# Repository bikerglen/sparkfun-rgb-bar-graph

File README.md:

Some notes:

Altera and Xilinx versions are the same except for the interface used to interface to the CPU. For Xilinx, it's an AXI4-Lite bus. For Intel/Altera it's an Avalon bus.

Minimum value of BASE_DELAY in both versions of code is 22 + (2 * (number of columns)). For the SparkFun RGB bar graph this is 22 + 2 * 16 =  22 + 32 = 54.

Refresh rate is calculated as

	(input clock frequency) / ((number of rows) * (BASE_DELAY) * (2^(bit depth) - 1)

For the SparkFun RGB LED bar graph this works out to

	(50e6) / (16 * 54 * (2^8 - 1)) = 227 Hz

For the DF Robot / Adafruit 64x64 RGB LED panels this works out to

	(50e6) / (32 * (22+2*64) * (2^6 - 1)) = 165 Hz

For my 96 x 64 video "wall" this works out to 

	(50e6) / (16 * 960 * (2^4 - 1)) = 217 Hz

In theory the base delay of 960 for these panels could be lowered to 22 + 2 * 192 = 406.

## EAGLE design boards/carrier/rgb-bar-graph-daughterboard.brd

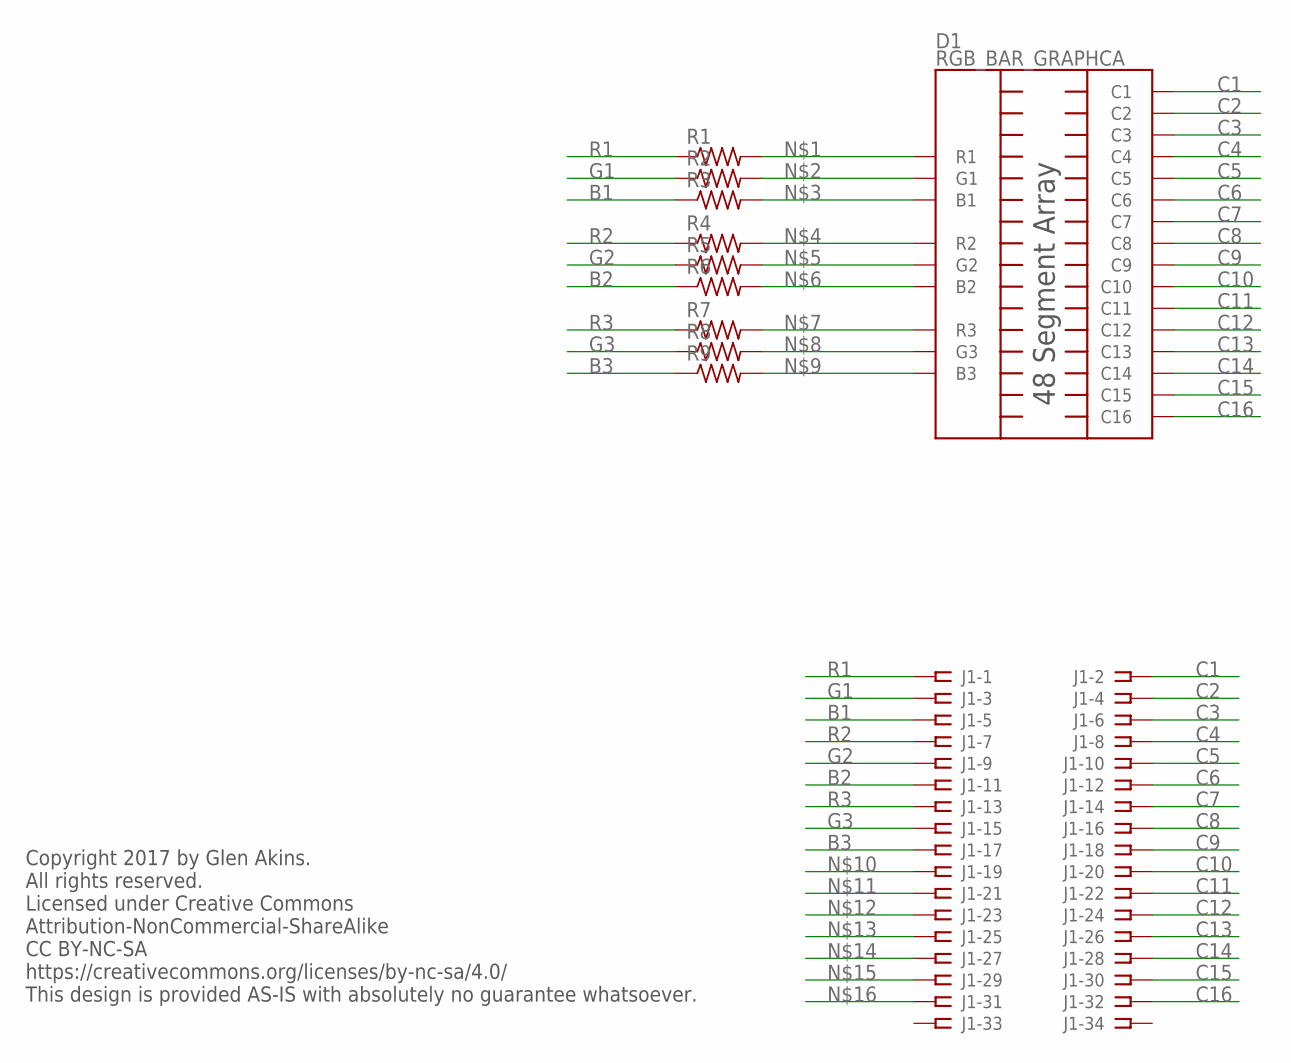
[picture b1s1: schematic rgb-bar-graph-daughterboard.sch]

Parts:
D1: RGB_BAR_GRAPHCA; RGB_BAR_GRAPH
J1: RGB-BAR-GRAPH-2X17-MOD-PADS; RGB-BAR-GRAPH-SMD-34-PIN
R1, R2, R3, R4, R5, R6, R7, R8, R9: R-US_R1206; R1206

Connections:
B1: J1.5, R3.1
B2: J1.11, R6.1
B3: J1.17, R9.1
C1: D1.1 (C1), J1.2
C2: D1.25 (C2), J1.4
C3: D1.3 (C3), J1.6
C4: D1.4 (C4), J1.8
C5: D1.23 (C5), J1.10
C6: D1.5 (C6), J1.12
C7: D1.22 (C7), J1.14
C8: D1.21 (C8), J1.16
C9: D1.20 (C9), J1.18
C10: D1.8 (C10), J1.20
C11: D1.19 (C11), J1.22
C12: D1.18 (C12), J1.24
C13: D1.10 (C13), J1.26
C14: D1.11 (C14), J1.28
C15: D1.15 (C15), J1.30
C16: D1.12 (C16), J1.32
G1: J1.3, R2.1
G2: J1.9, R5.1
G3: J1.15, R8.1
unnamed: D1.9 (R1), R1.2
unnamed: D1.7 (G1), R2.2
unnamed: D1.24 (B1), R3.2
unnamed: D1.17 (R2), R4.2
unnamed: D1.16 (G2), R5.2
unnamed: D1.6 (B2), R6.2
unnamed: D1.13 (R3), R7.2
unnamed: D1.2 (G3), R8.2
unnamed: D1.14 (B3), R9.2
R1: J1.1, R1.1
R2: J1.7, R4.1
R3: J1.13, R7.1

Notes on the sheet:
Copyright 2017 by Glen Akins. All rights reserved. Licensed under Creative Commons Attribution-NonCommercial-ShareAlike CC BY-NC-SA https://creativecommons.org/licenses/by-nc-sa/4.0/ This design is provided AS-IS with absolutely no guarantee whatsoever.

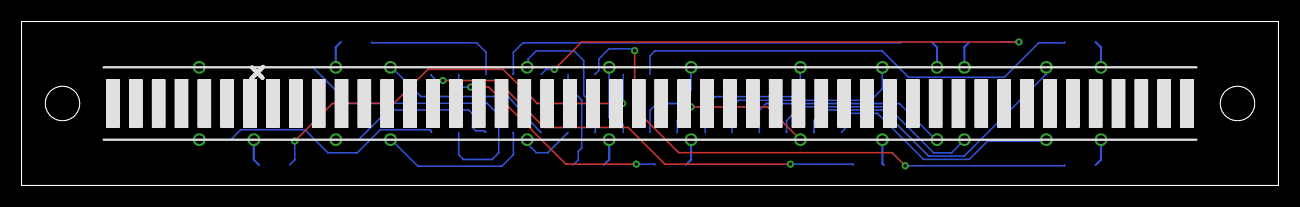
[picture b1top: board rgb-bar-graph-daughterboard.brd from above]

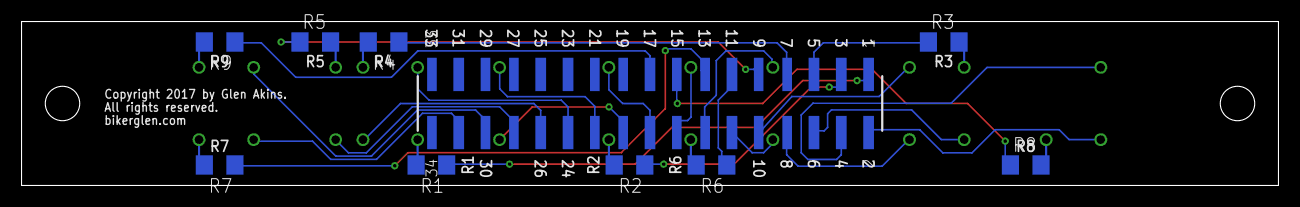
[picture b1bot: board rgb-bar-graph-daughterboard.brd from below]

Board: 2 copper layers, 116.8 x 15.2 mm, 11 parts (10 on the bottom side), 34 nets.

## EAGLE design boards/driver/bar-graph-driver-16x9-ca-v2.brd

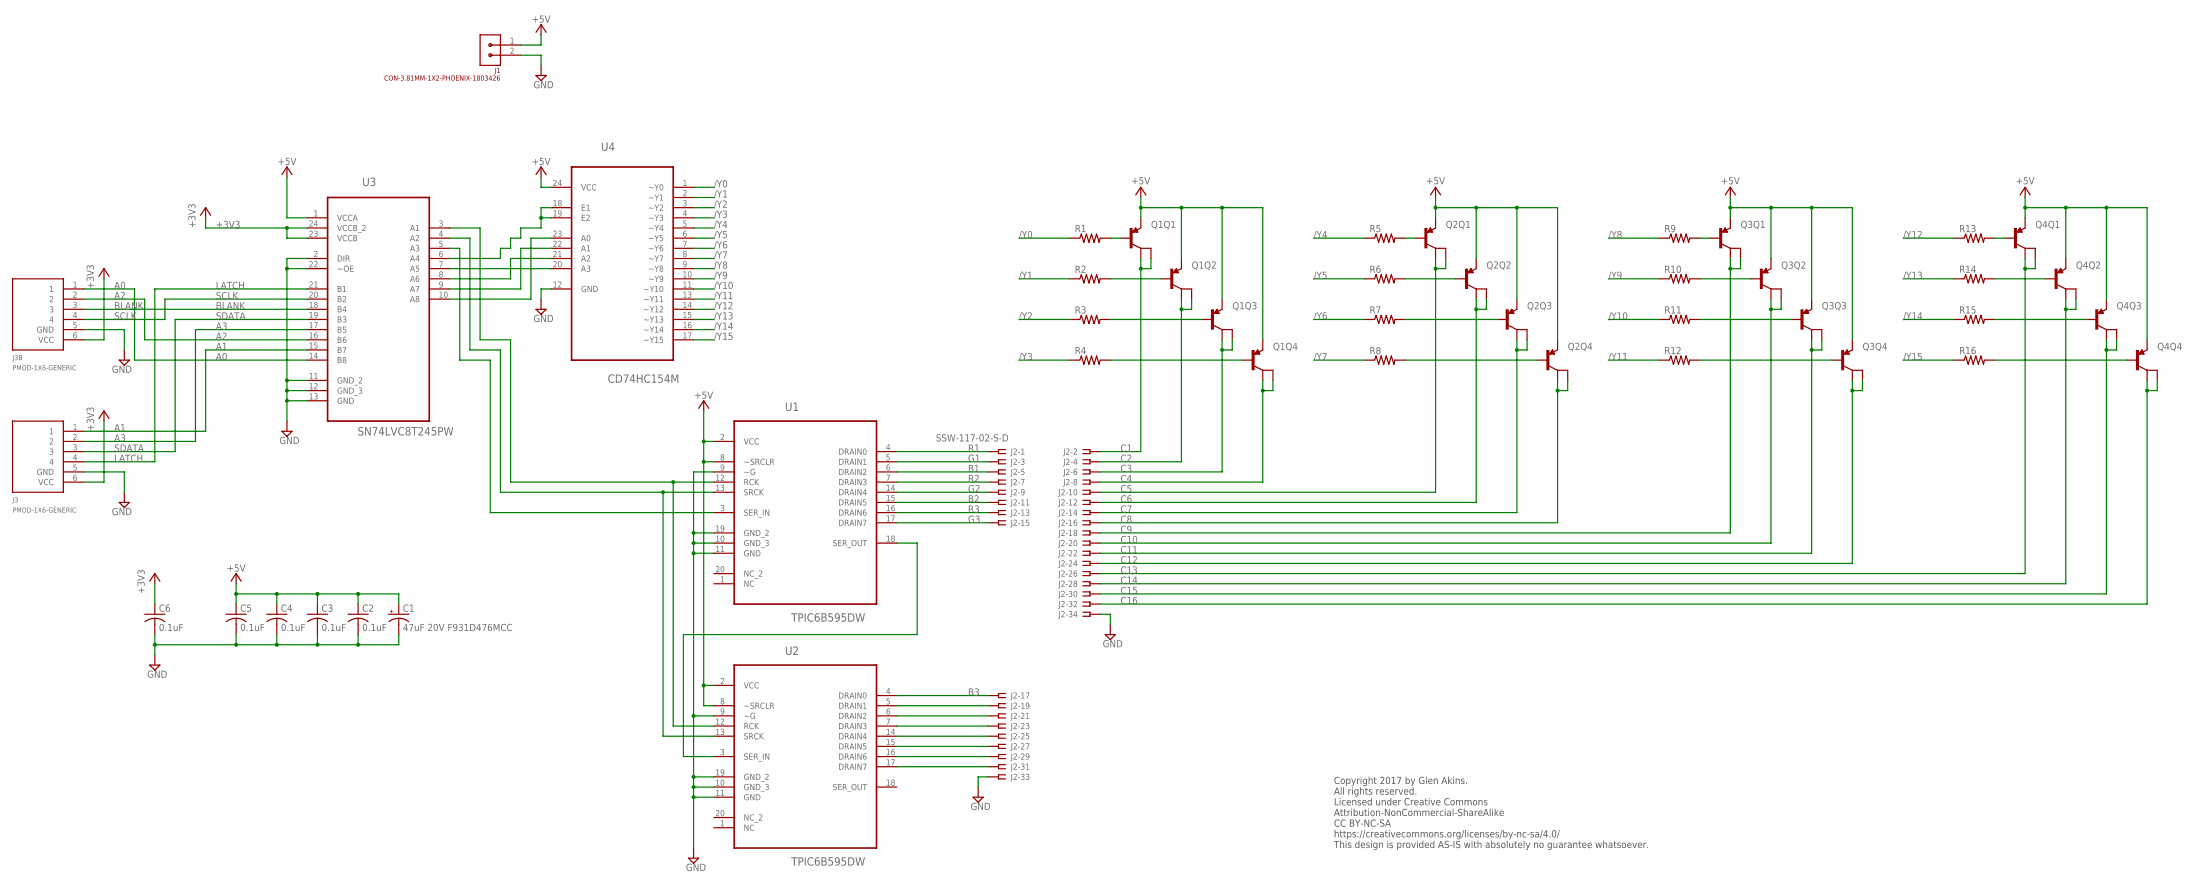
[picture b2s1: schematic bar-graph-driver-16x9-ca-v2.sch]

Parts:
C1: 47uF 20V F931D476MCC; C/6032-28R
C2, C3, C4, C5, C6: 0.1uF; C1206
J1: CON-3.81MM-1X2-PHOENIX-1803426; CON-PHOENIX-1803426-3.81-1X2
J2: SSW-117-02-S-D
J3, J3B: PMOD-1X6-GENERIC; CON-PMOD-1X6
Q1, Q2, Q3, Q4: MMPQ2907A; SO16
R1, R2, R3, R4, R5, R6, R7, R8, R9, R10, R11, R12, R13, R14, R15, R16: R-US_R1206; R1206
U1, U2: TPIC6B595DW; SOIC127P1030X265-20N
U3: SN74LVC8T245PW; SOP65P640X120-24N
U4: CD74HC154M; SOIC127P1030X265-24N

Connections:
+3V3: C6.1, J3.6 (VCC), J3B.6 (VCC), U3.23 (VCCB), U3.24 (VCCB_2)
+5V: C1.+, C2.1, C3.1, C4.1, C5.1, J1.1, Q1.10 (E), Q1.12 (E), Q1.14 (E), Q1.16 (E), Q2.10 (E), Q2.12 (E), Q2.14 (E), Q2.16 (E), Q3.10 (E), Q3.12 (E), Q3.14 (E), Q3.16 (E), Q4.10 (E), Q4.12 (E), Q4.14 (E), Q4.16 (E), U1.2 (VCC), U1.8 (~SRCLR), U2.2 (VCC), U2.8 (~SRCLR), U3.1 (VCCA), U4.24 (VCC)
/Y0: R1.1, U4.1 (~Y0)
/Y1: R2.1, U4.2 (~Y1)
/Y2: R3.1, U4.3 (~Y2)
/Y3: R4.1, U4.4 (~Y3)
/Y4: R5.1, U4.5 (~Y4)
/Y5: R6.1, U4.6 (~Y5)
/Y6: R7.1, U4.7 (~Y6)
/Y7: R8.1, U4.8 (~Y7)
/Y8: R9.1, U4.9 (~Y8)
/Y9: R10.1, U4.10 (~Y9)
/Y10: R11.1, U4.11 (~Y10)
/Y11: R12.1, U4.13 (~Y11)
/Y12: R13.1, U4.14 (~Y12)
/Y13: R14.1, U4.15 (~Y13)
/Y14: R15.1, U4.16 (~Y14)
/Y15: R16.1, U4.17 (~Y15)
A0: J3B.1, U3.14 (B8)
A0_5: U3.10 (A8), U4.23 (A0)
A1: J3.1, U3.15 (B7)
A1_5: U3.9 (A7), U4.22 (A1)
A2: J3B.2, U3.16 (B6)
A2_5: U3.8 (A6), U4.21 (A2)
A3: J3.2, U3.17 (B5)
A3_5: U3.7 (A5), U4.20 (A3)
B1: J2.5, U1.6 (DRAIN2)
B2: J2.11, U1.15 (DRAIN5)
B3: J2.17, U2.4 (DRAIN0)
BLANK: J3B.3, U3.18 (B4)
BLANK_5: U3.6 (A4), U4.18 (E1), U4.19 (E2)
C1: J2.2, Q1.1 (C), Q1.2 (C)
C2: J2.4, Q1.3 (C), Q1.4 (C)
C3: J2.6, Q1.5 (C), Q1.6 (C)
C4: J2.8, Q1.7 (C), Q1.8 (C)
C5: J2.10, Q2.1 (C), Q2.2 (C)
C6: J2.12, Q2.3 (C), Q2.4 (C)
C7: J2.14, Q2.5 (C), Q2.6 (C)
C8: J2.16, Q2.7 (C), Q2.8 (C)
C9: J2.18, Q3.1 (C), Q3.2 (C)
C10: J2.20, Q3.3 (C), Q3.4 (C)
C11: J2.22, Q3.5 (C), Q3.6 (C)
C12: J2.24, Q3.7 (C), Q3.8 (C)
C13: J2.26, Q4.1 (C), Q4.2 (C)
C14: J2.28, Q4.3 (C), Q4.4 (C)
C15: J2.30, Q4.5 (C), Q4.6 (C)
C16: J2.32, Q4.7 (C), Q4.8 (C)
G1: J2.3, U1.5 (DRAIN1)
G2: J2.9, U1.14 (DRAIN4)
G3: J2.15, U1.17 (DRAIN7)
GND: C1.-, C2.2, C3.2, C4.2, C5.2, C6.2, J1.2, J2.33, J2.34, J3.5 (GND), J3B.5 (GND), U1.9 (~G), U1.10 (GND_3), U1.11 (GND), U1.19 (GND_2), U2.9 (~G), U2.10 (GND_3), U2.11 (GND), U2.19 (GND_2), U3.2 (DIR), U3.11 (GND_2), U3.12 (GND_3), U3.13 (GND), U3.22 (~OE), U4.12 (GND)
LATCH: J3.4, U3.21 (B1)
LATCH_5: U1.12 (RCK), U2.12 (RCK), U3.3 (A1)
unnamed: U1.18 (SER_OUT), U2.3 (SER_IN)
unnamed: J2.19, U2.5 (DRAIN1)
unnamed: J2.21, U2.6 (DRAIN2)
unnamed: J2.23, U2.7 (DRAIN3)
unnamed: J2.25, U2.14 (DRAIN4)
unnamed: J2.27, U2.15 (DRAIN5)
unnamed: J2.29, U2.16 (DRAIN6)
unnamed: J2.31, U2.17 (DRAIN7)
unnamed: Q1.13 (B), R2.2
unnamed: Q1.11 (B), R3.2
unnamed: Q1.9 (B), R4.2
unnamed: Q1.15 (B), R1.2
unnamed: Q2.13 (B), R6.2
unnamed: Q2.11 (B), R7.2
unnamed: Q2.9 (B), R8.2
unnamed: Q2.15 (B), R5.2
unnamed: Q3.13 (B), R10.2
unnamed: Q3.11 (B), R11.2
unnamed: Q3.9 (B), R12.2
unnamed: Q3.15 (B), R9.2
unnamed: Q4.13 (B), R14.2
unnamed: Q4.11 (B), R15.2
unnamed: Q4.9 (B), R16.2
unnamed: Q4.15 (B), R13.2
R1: J2.1, U1.4 (DRAIN0)
R2: J2.7, U1.7 (DRAIN3)
R3: J2.13, U1.16 (DRAIN6)
SCLK: J3B.4, U3.20 (B2)
SCLK_5: U1.13 (SRCK), U2.13 (SRCK), U3.4 (A2)
SDATA: J3.3, U3.19 (B3)
SDATA_5: U1.3 (SER_IN), U3.5 (A3)

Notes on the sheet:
Copyright 2017 by Glen Akins. All rights reserved. Licensed under Creative Commons Attribution-NonCommercial-ShareAlike CC BY-NC-SA https://creativecommons.org/licenses/by-nc-sa/4.0/ This design is provided AS-IS with absolutely no guarantee whatsoever.

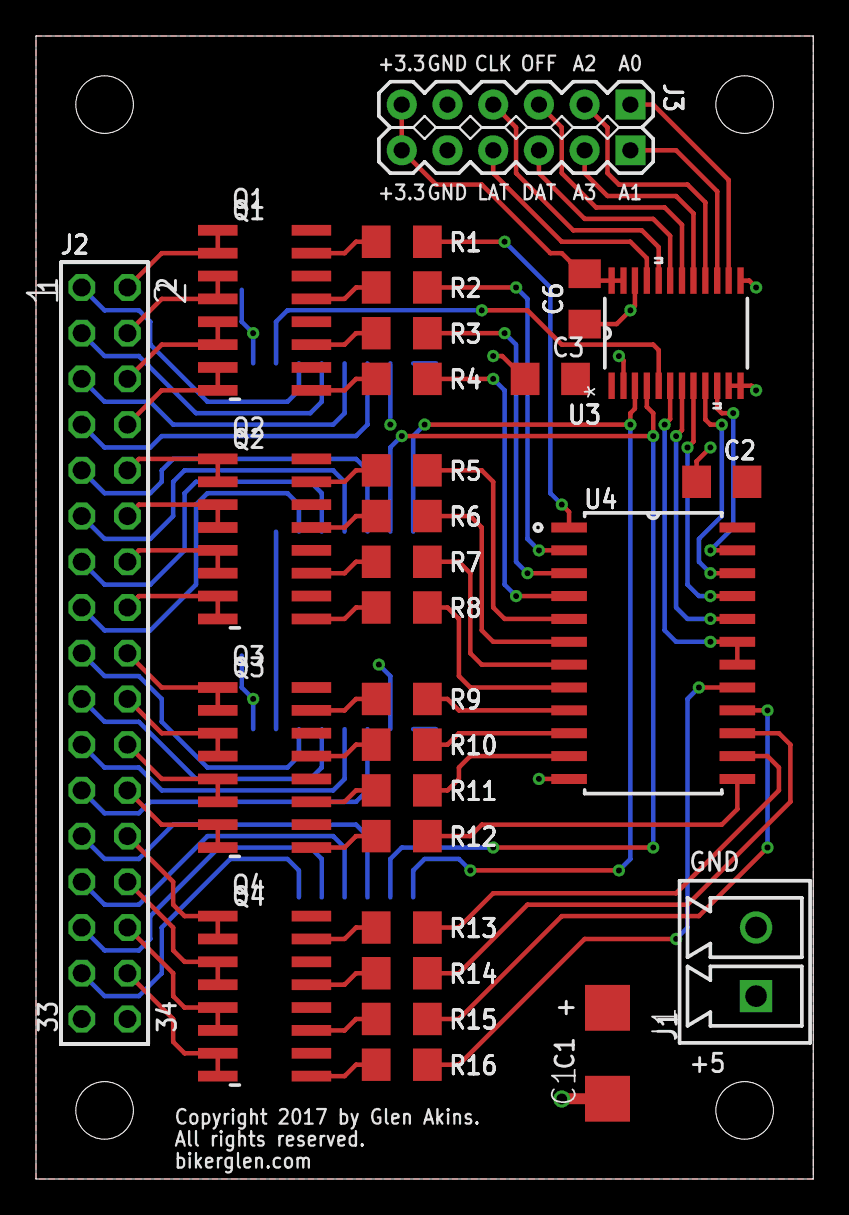
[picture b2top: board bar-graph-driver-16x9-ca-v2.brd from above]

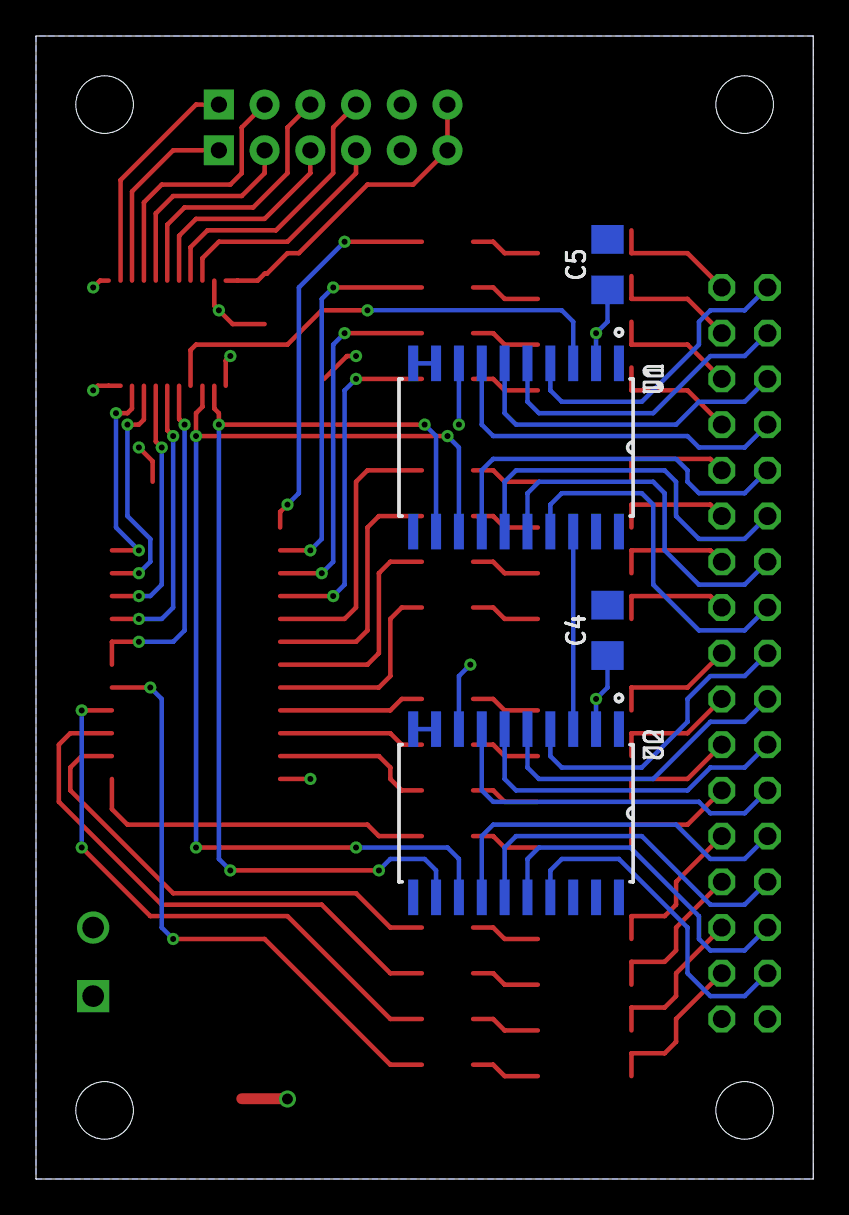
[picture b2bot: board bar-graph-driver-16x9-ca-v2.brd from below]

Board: 2 copper layers, 43.2 x 63.5 mm, 34 parts (4 on the bottom side), 84 nets.

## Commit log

2017-03-17 added copyright messages, fixed labels on swapped pins on data connector versus initial run of fabbed boards
2017-03-17 added photo of board
2017-04-01 initial checkin of FPGA RTL and Microblaze software.
2017-04-01 adding constraints with pinout for arty board's JA PMOD connector.
2017-07-23 initial checkin of teensy 3.2 / SmartMatrix version
2017-07-23 fixed pin number
2018-02-23 updated RTL to allow scan rate to be changed, renamed to add separate xilinx and altera/intel rtl directories
2018-02-23 adding avalon bus version of code for Intel/Altera FPGAs
2018-02-23 added readme file
2018-02-23 fixed error because video wall is implemented as 16 rows x 192 columns
2018-02-23 adding nios ii software
2018-02-25 adding top level design with alt_pll component and NIOS II embedded system.
2023-06-13 increase blanking time to eliminate ghosting caused by slow switching of PNP transistors

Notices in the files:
parts and their libraries:
SparkFun-LED: Licensing: Creative Commons ShareAlike 4.0 International - https://creativecommons.org/licenses/by-sa/4.0
